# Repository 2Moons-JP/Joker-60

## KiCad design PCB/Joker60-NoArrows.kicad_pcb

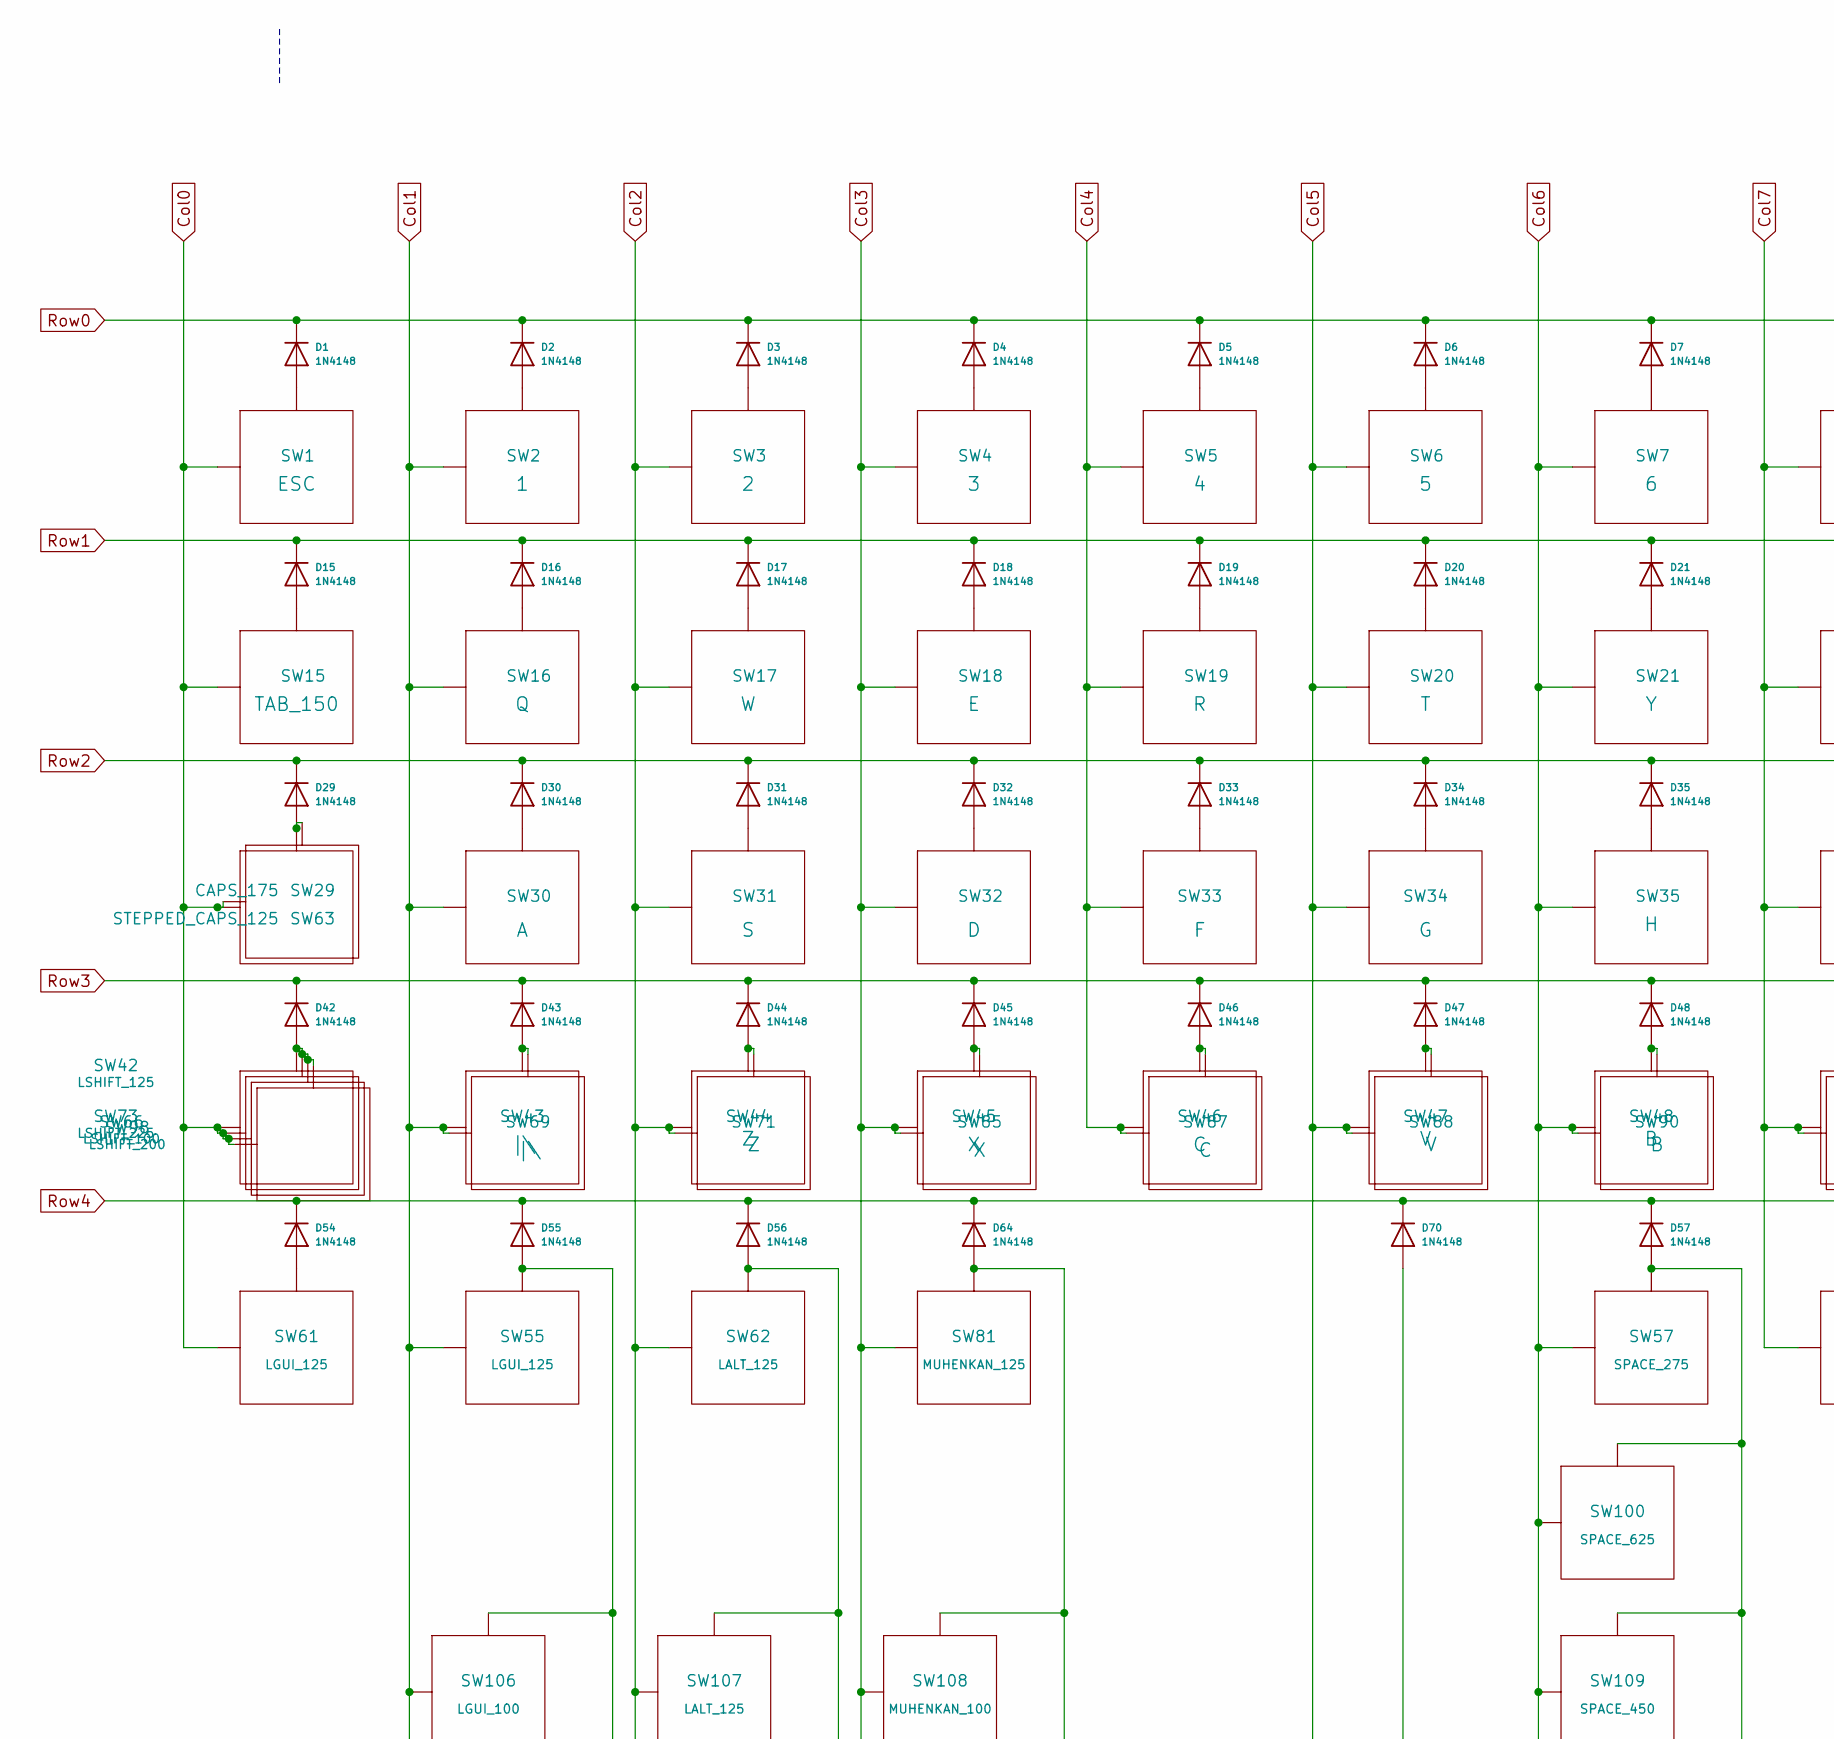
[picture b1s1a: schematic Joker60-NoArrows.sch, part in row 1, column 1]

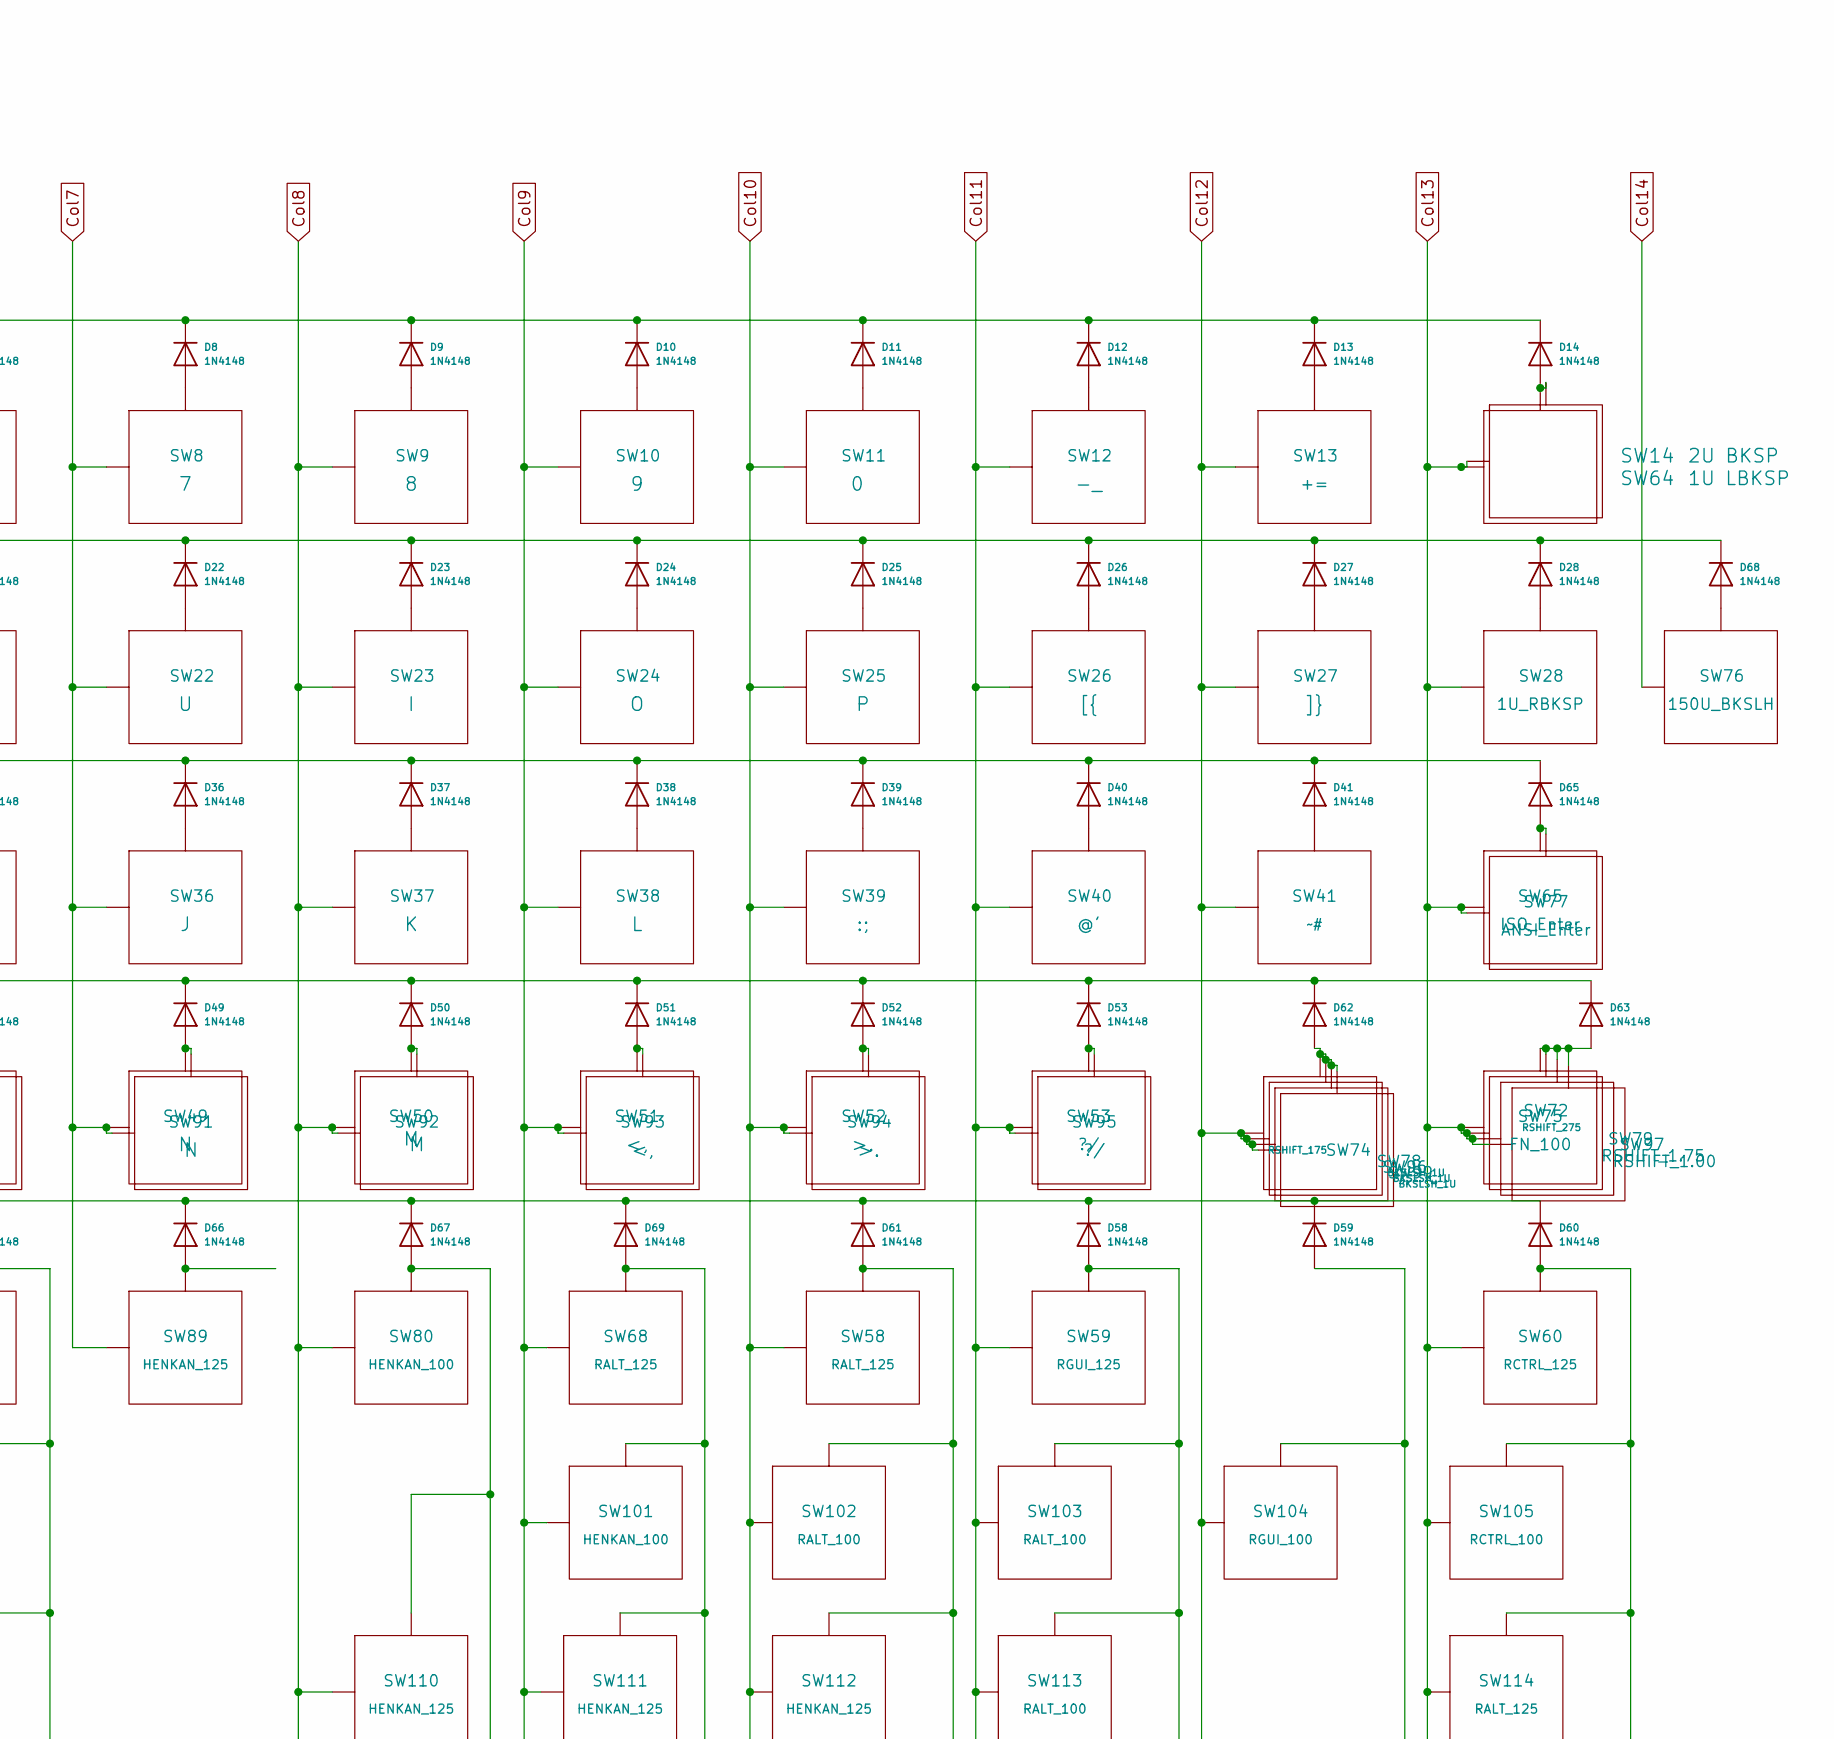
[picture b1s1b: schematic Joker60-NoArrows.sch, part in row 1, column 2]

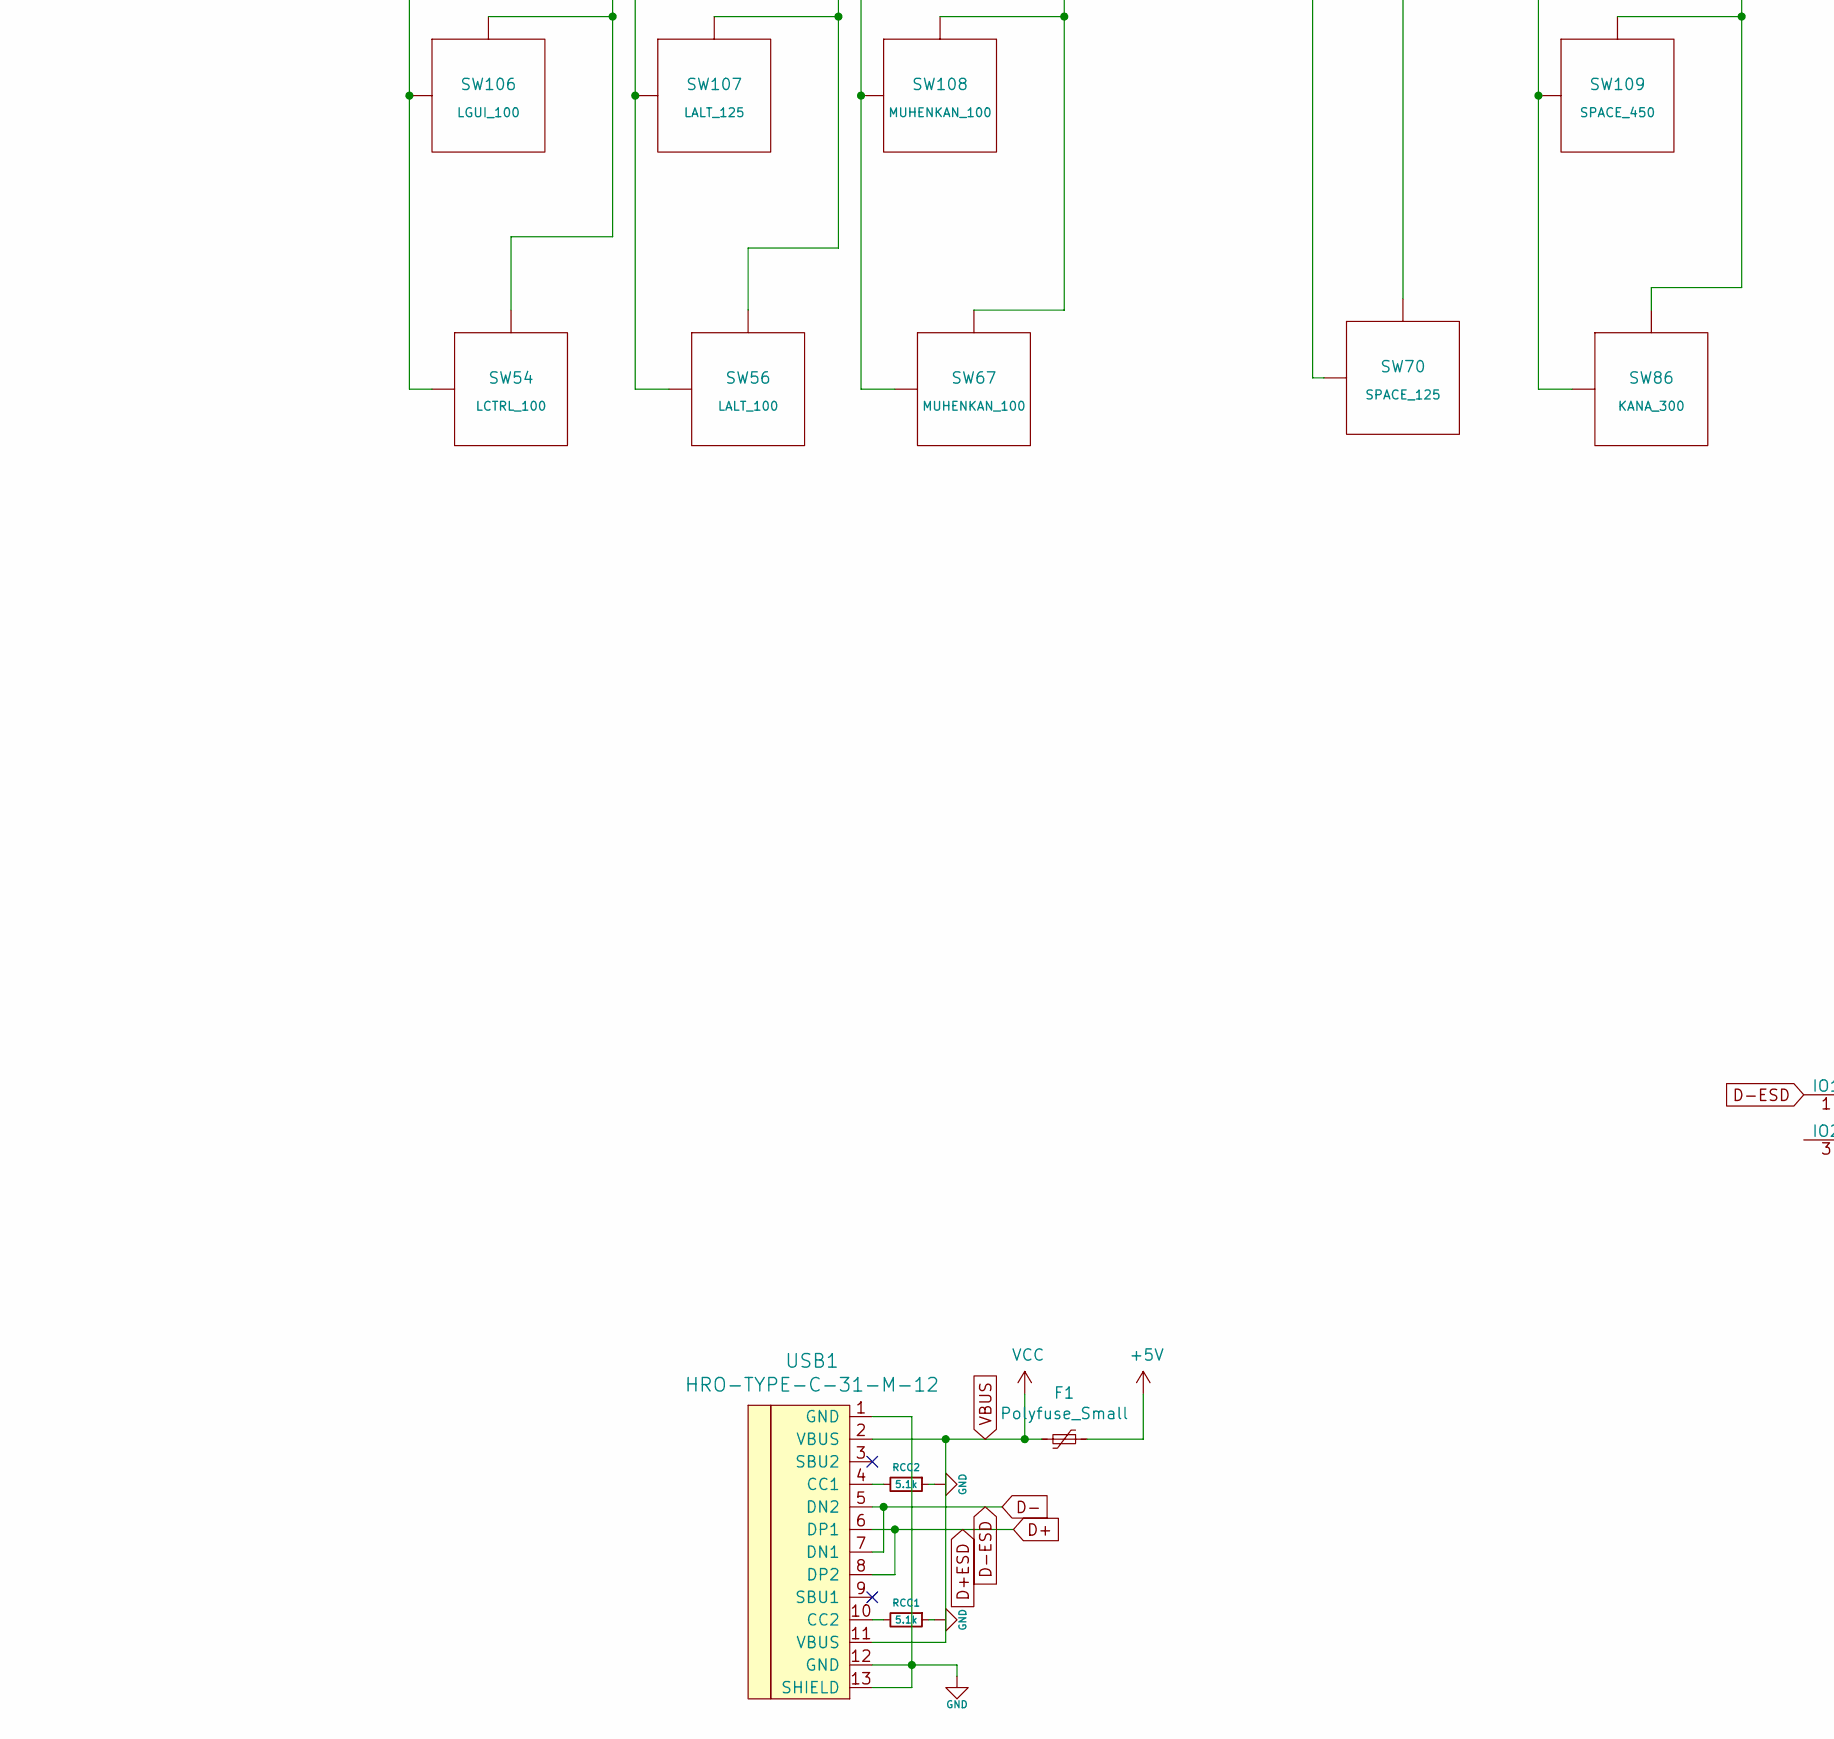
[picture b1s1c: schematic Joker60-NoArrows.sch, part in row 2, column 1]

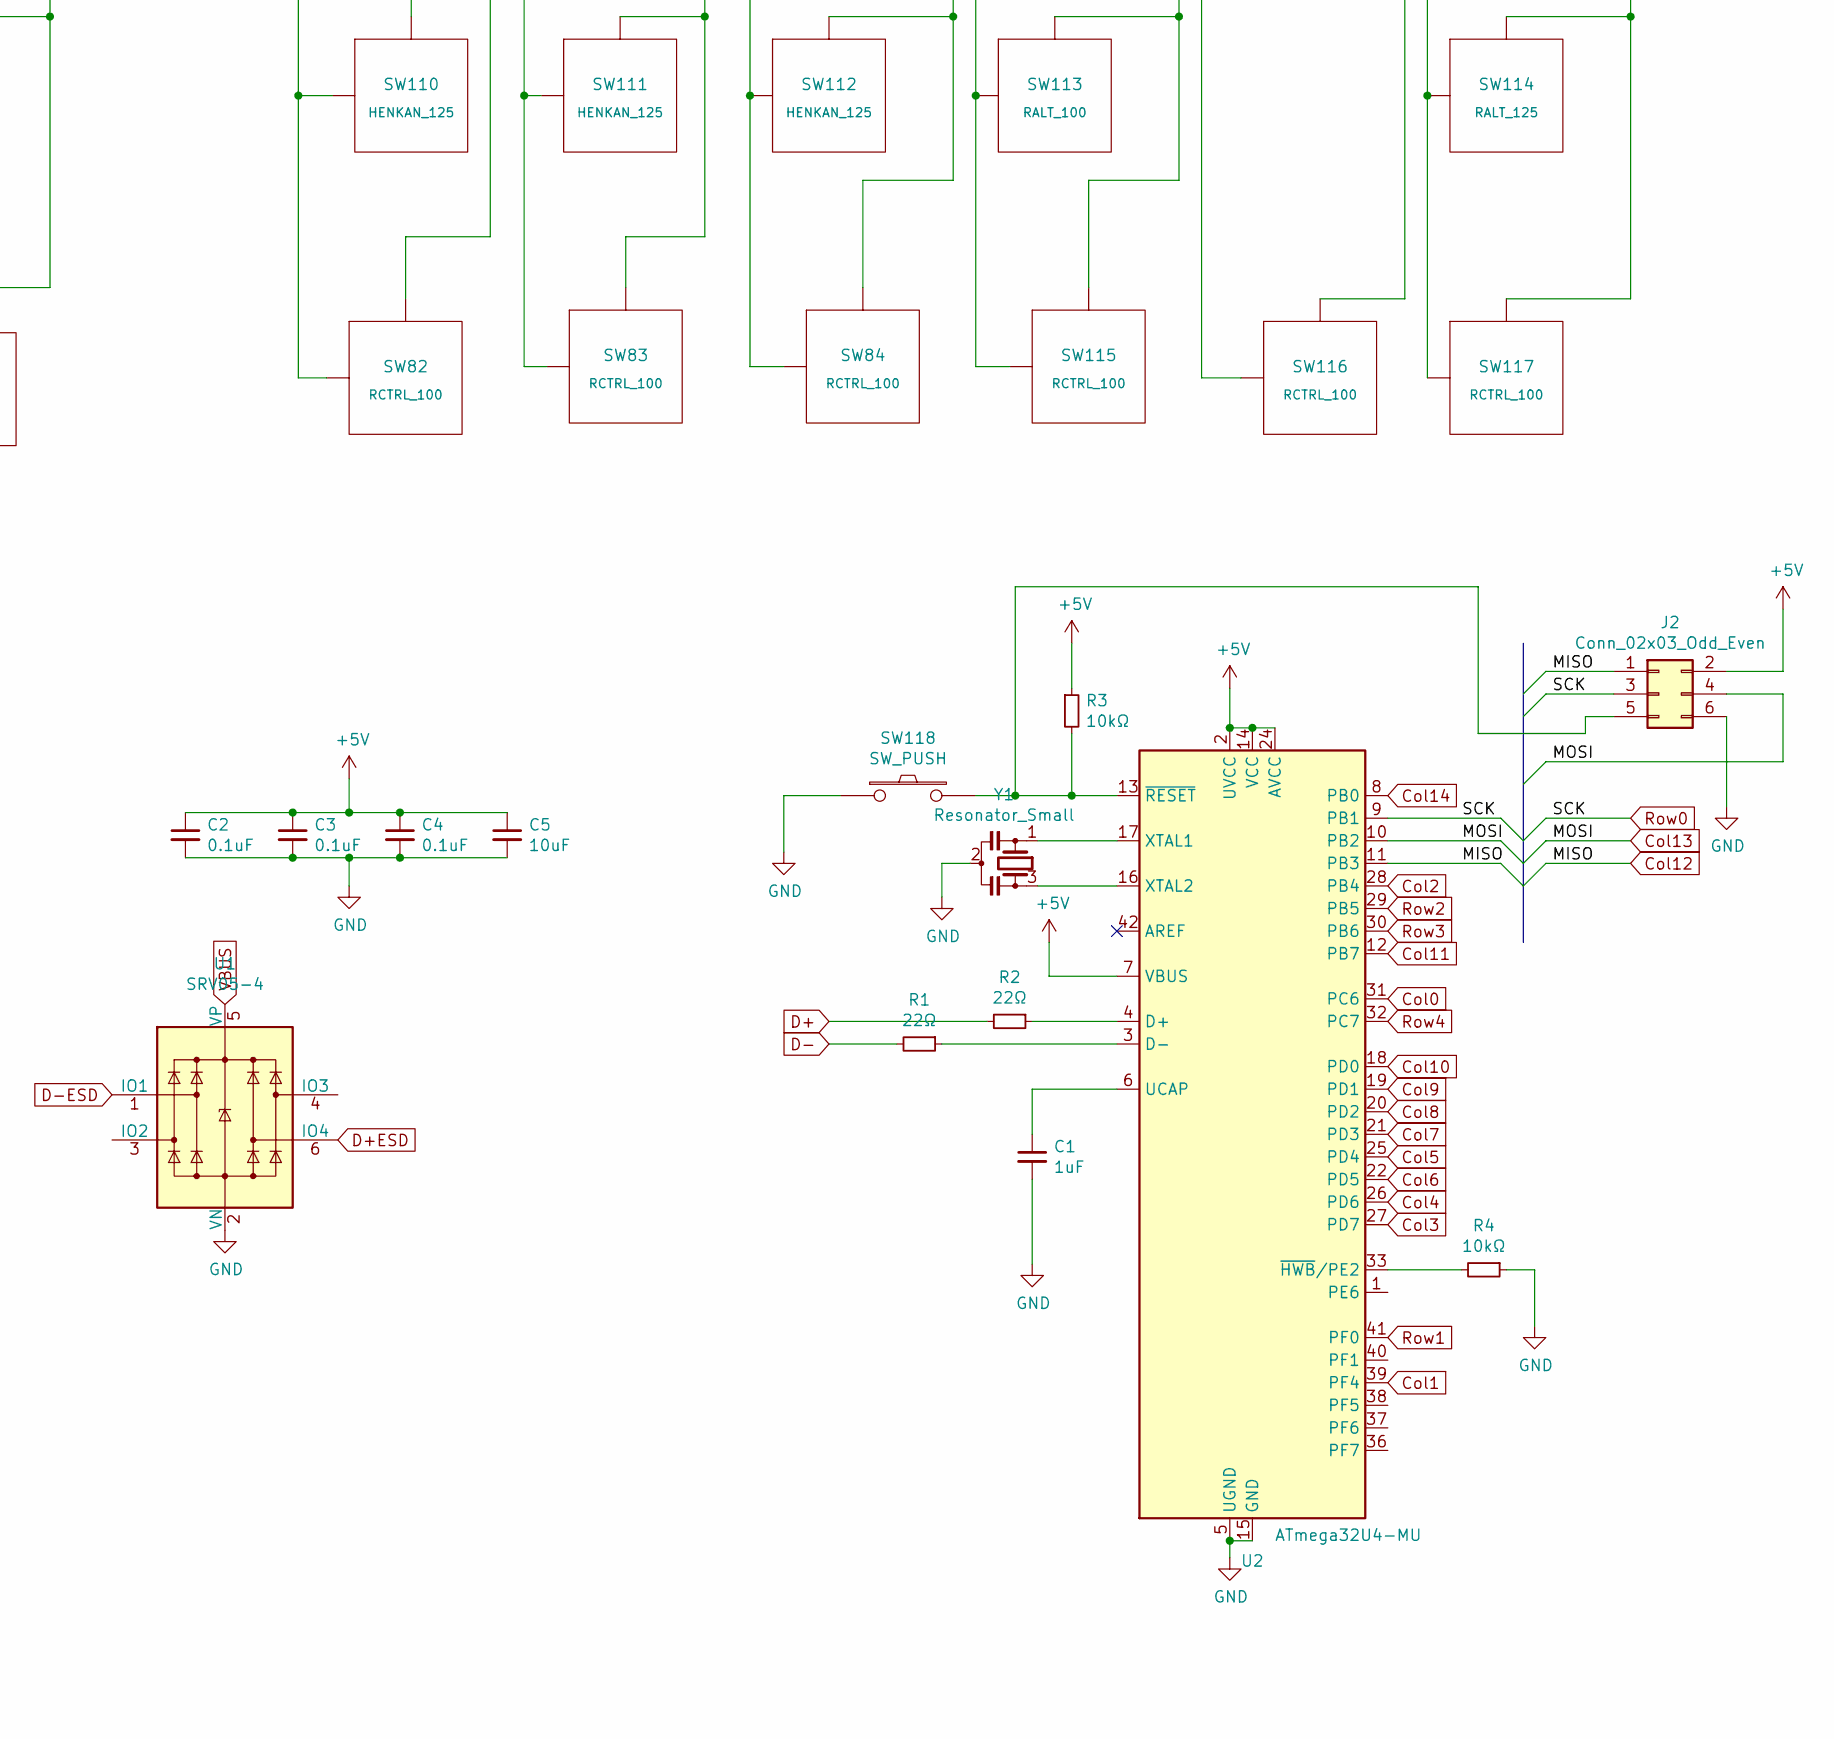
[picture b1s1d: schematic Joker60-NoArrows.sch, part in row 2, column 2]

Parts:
C1: 1uF; C_0603_1608Metric; Part# CL10A105KB8NNNC; LCSC Part# C15849
C2, C3, C4: 0.1uF; C_0603_1608Metric; Part# CC0603KRX7R9BB104; LCSC Part# C14663
C5: 10uF; C_0603_1608Metric; Part# CL10C150JB8NNNC; LCSC Part# C1644
D1, D2, D3, D4, D5, D6, D7, D8, D9, D10, D11, D12, D13, D14, D15, D16, D17, D18, D19, D20, D21, D22, D23, D24, D25, D26, D27, D28, D29, D30, D31, D32, D33, D34, D35, D36, D37, D38, D39, D40, D41, D42, D43, D44, D45, D46, D47, D48, D49, D50, D51, D52, D53, D54, D55, D56, D57, D58, D59, D60, D61, D62, D63, D64, D65, D66, D67, D68, D69, D70: 1N4148; D_SOD-123; Part# 1N4148W; LCSC Part# C444720
F1: Polyfuse_Small; Fuse_0805_2012Metric; Part# nSMD025; LCSC Part# C70068
J2: Conn_02x03_Odd_Even; PinHeader_2x03_P2.54mm_Vertical
R1, R2: 22Ω; R_0603_1608Metric; Part# 0603WAJ0220T5E; LCSC Part# C1203
R3, R4: 10kΩ; R_0603_1608Metric; Part# RMC 0603 10K F N; LCSC Part# C269701
RCC1, RCC2: 5.1k; R_0805_2012Metric; Part# PTFR1206B5K10P9; LCSC Part# C351456
SW1: ESC; MX100
SW2: 1; MX100
SW3: 2; MX100
SW4: 3; MX100
SW5: 4; MX100
SW6: 5; MX100
SW7: 6; MX100
SW8: 7; MX100
SW9: 8; MX100
SW10: 9; MX100
SW11: 0; MX100
SW12: -_; MX100
SW13: +=; MX100
SW14: 2U BKSP; MX200
SW15: TAB_150; MX150
SW16: Q; MX100
SW17: W; MX100
SW18: E; MX100
SW19: R; MX100
SW20: T; MX100
SW21: Y; MX100
SW22: U; MX100
SW23: I; MX100
SW24: O; MX100
SW25: P; MX100
SW26: [{; MX100
SW27: ]}; MX100
SW28: 1U_RBKSP; MX100
SW29: CAPS_175; MX175
SW30: A; MX100
SW31: S; MX100
SW32: D; MX100
SW33: F; MX100
SW34: G; MX100
SW35: H; MX100
SW36: J; MX100
SW37: K; MX100
SW38: L; MX100
SW39: :;; MX100
SW40: @'; MX100
SW41: ~~#; MX100
SW42: LSHIFT_125; MX125
SW43, SW69: |\\; MX100
SW44, SW71: Z; MX100
SW45, SW85: X; MX100
SW46, SW87: C; MX100
SW47, SW88: V; MX100
SW48, SW90: B; MX100
SW49, SW91: N; MX100
SW50, SW92: M; MX100
SW51, SW93: <,; MX100
SW52, SW94: >.; MX100
SW53, SW95: ?/; MX100
SW54: LCTRL_100; MX100
SW55, SW61: LGUI_125; MX125
SW56: LALT_100; MX100
SW57: SPACE_275; MX275R
SW58, SW68, SW114: RALT_125; MX125
SW59: RGUI_125; MX125
SW60: RCTRL_125; MX125
SW62, SW107: LALT_125; MX125
SW63: STEPPED_CAPS_125; MX125
SW64: 1U LBKSP; MX100
SW65: ISO_Enter; MX_ISOEnter_Vertical
SW66: LSHIFT_100; MX100
SW67, SW108: MUHENKAN_100; MX100
SW70: SPACE_125; MX125
SW72: RSHIFT_275; MX275R
SW73: LSHIFT_225; MX225R
SW74: RSHIFT_175; MX175
SW75: FN_100; MX100
SW76: 150U_BKSLH; MX150
SW77: ANSI_Enter; MX225
SW78, SW99: BKSLSH_1U; MX100
SW79: RSHIFT_1.75; MX175
SW80, SW101: HENKAN_100; MX100
SW81: MUHENKAN_125; MX125
SW82, SW83, SW84, SW105, SW115, SW116, SW117: RCTRL_100; MX100
SW86: KANA_300; MX300R
SW89, SW110, SW111, SW112: HENKAN_125; MX125
SW96: BKSLSH_1U; MX200
SW97: RSHIFT_1.00; MX100
SW98: LSHIFT_200; MX200R
SW100: SPACE_625; MX625R
SW102, SW103, SW113: RALT_100; MX100
SW104: RGUI_100; MX100
SW106: LGUI_100; MX100
SW109: SPACE_450; MX450R
SW118: SW_PUSH; SKQG-1155865
U1: SRV05-4; SOT-23-6; Part# SRV05-4; LCSC Part# C558418
U2: ATmega32U4-MU; QFN-44-1EP_7x7mm_P0.5mm_EP5.2x5.2mm; Part# ATMEGA32U4-MU; LCSC Part# C112161
USB1: HRO-TYPE-C-31-M-12; HRO-TYPE-C-31-M-12-Assembly; Part# TYPE-C-31-M-12; LCSC Part# C165948
Y1: Resonator_Small; Resonator_SMD_muRata_CSTxExxV-3Pin_3.0x1.1mm_HandSoldering_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; Part# CSTNE16MOV530000R0; LCSC Part# C341521

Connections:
+5V: C2.1, C3.1, C4.1, C5.1, F1.1, J2.2, R3.1, U2.2 (UVCC), U2.7 (VBUS), U2.14 (VCC), U2.24 (AVCC), U2.34 (VCC), U2.44 (AVCC)
Col0: SW1.1 (Col), SW15.1 (Col), SW29.1 (Col), SW42.1 (Col), SW61.1 (Col), SW63.1 (Col), SW66.1 (Col), SW73.1 (Col), SW98.1 (Col), U2.31 (PC6)
Col1: SW2.1 (Col), SW16.1 (Col), SW30.1 (Col), SW43.1 (Col), SW54.1 (Col), SW55.1 (Col), SW69.1 (Col), SW106.1 (Col), U2.39 (PF4)
Col2: SW3.1 (Col), SW17.1 (Col), SW31.1 (Col), SW44.1 (Col), SW56.1 (Col), SW62.1 (Col), SW71.1 (Col), SW107.1 (Col), U2.28 (PB4)
Col3: SW4.1 (Col), SW18.1 (Col), SW32.1 (Col), SW45.1 (Col), SW67.1 (Col), SW81.1 (Col), SW85.1 (Col), SW108.1 (Col), U2.27 (PD7)
Col4: SW5.1 (Col), SW19.1 (Col), SW33.1 (Col), SW46.1 (Col), SW87.1 (Col), U2.26 (PD6)
Col5: SW6.1 (Col), SW20.1 (Col), SW34.1 (Col), SW47.1 (Col), SW70.1 (Col), SW88.1 (Col), U2.25 (PD4)
Col6: SW7.1 (Col), SW21.1 (Col), SW35.1 (Col), SW48.1 (Col), SW57.1 (Col), SW86.1 (Col), SW90.1 (Col), SW100.1 (Col), SW109.1 (Col), U2.22 (PD5)
Col7: SW8.1 (Col), SW22.1 (Col), SW36.1 (Col), SW49.1 (Col), SW89.1 (Col), SW91.1 (Col), U2.21 (PD3)
Col8: SW9.1 (Col), SW23.1 (Col), SW37.1 (Col), SW50.1 (Col), SW80.1 (Col), SW82.1 (Col), SW92.1 (Col), SW110.1 (Col), U2.20 (PD2)
Col9: SW10.1 (Col), SW24.1 (Col), SW38.1 (Col), SW51.1 (Col), SW68.1 (Col), SW83.1 (Col), SW93.1 (Col), SW101.1 (Col), SW111.1 (Col), U2.19 (PD1)
Col10: SW11.1 (Col), SW25.1 (Col), SW39.1 (Col), SW52.1 (Col), SW58.1 (Col), SW84.1 (Col), SW94.1 (Col), SW102.1 (Col), SW112.1 (Col), U2.18 (PD0)
Col11: SW12.1 (Col), SW26.1 (Col), SW40.1 (Col), SW53.1 (Col), SW59.1 (Col), SW95.1 (Col), SW103.1 (Col), SW113.1 (Col), SW115.1 (Col), U2.12 (PB7)
Col12: J2.1, SW13.1 (Col), SW27.1 (Col), SW41.1 (Col), SW74.1 (Col), SW78.1 (Col), SW96.1 (Col), SW99.1 (Col), SW104.1 (Col), SW116.1 (Col), U2.11 (PB3)
Col13: J2.4, SW14.1 (Col), SW28.1 (Col), SW60.1 (Col), SW64.1 (Col), SW65.1 (Col), SW72.1 (Col), SW75.1 (Col), SW77.1 (Col), SW79.1 (Col), SW97.1 (Col), SW105.1 (Col), SW114.1 (Col), SW117.1 (Col), U2.10 (PB2)
Col14: SW76.1 (Col), U2.8 (PB0)
D+: R2.2, U1.6 (IO4), USB1.6 (DP1), USB1.8 (DP2)
D-: R1.2, U1.1 (IO1), USB1.5 (DN2), USB1.7 (DN1)
GND: C1.2, C2.2, C3.2, C4.2, C5.2, J2.6, R4.1, RCC1.1, RCC2.1, SW118.1, U1.2 (VN), U2.5 (UGND), U2.15 (GND), U2.23 (GND), U2.35 (GND), U2.43 (GND), U2.45 (GND), USB1.1 (GND), USB1.12 (GND), USB1.13 (SHIELD), Y1.2
unnamed: C1.1, U2.6 (UCAP)
unnamed: D1.2 (A), SW1.2 (Row)
unnamed: D2.2 (A), SW2.2 (Row)
unnamed: D3.2 (A), SW3.2 (Row)
unnamed: D4.2 (A), SW4.2 (Row)
unnamed: D5.2 (A), SW5.2 (Row)
unnamed: D6.2 (A), SW6.2 (Row)
unnamed: D7.2 (A), SW7.2 (Row)
unnamed: D8.2 (A), SW8.2 (Row)
unnamed: D9.2 (A), SW9.2 (Row)
unnamed: D10.2 (A), SW10.2 (Row)
unnamed: D11.2 (A), SW11.2 (Row)
unnamed: D12.2 (A), SW12.2 (Row)
unnamed: D13.2 (A), SW13.2 (Row)
unnamed: D14.2 (A), SW14.2 (Row), SW64.2 (Row)
unnamed: D15.2 (A), SW15.2 (Row)
unnamed: D16.2 (A), SW16.2 (Row)
unnamed: D17.2 (A), SW17.2 (Row)
unnamed: D18.2 (A), SW18.2 (Row)
unnamed: D19.2 (A), SW19.2 (Row)
unnamed: D20.2 (A), SW20.2 (Row)
unnamed: D21.2 (A), SW21.2 (Row)
unnamed: D22.2 (A), SW22.2 (Row)
unnamed: D23.2 (A), SW23.2 (Row)
unnamed: D24.2 (A), SW24.2 (Row)
unnamed: D25.2 (A), SW25.2 (Row)
unnamed: D26.2 (A), SW26.2 (Row)
unnamed: D27.2 (A), SW27.2 (Row)
unnamed: D28.2 (A), SW28.2 (Row)
unnamed: D29.2 (A), SW29.2 (Row), SW63.2 (Row)
unnamed: D30.2 (A), SW30.2 (Row)
unnamed: D31.2 (A), SW31.2 (Row)
unnamed: D32.2 (A), SW32.2 (Row)
unnamed: D33.2 (A), SW33.2 (Row)
unnamed: D34.2 (A), SW34.2 (Row)
unnamed: D35.2 (A), SW35.2 (Row)
unnamed: D36.2 (A), SW36.2 (Row)
unnamed: D37.2 (A), SW37.2 (Row)
unnamed: D38.2 (A), SW38.2 (Row)
unnamed: D39.2 (A), SW39.2 (Row)
unnamed: D40.2 (A), SW40.2 (Row)
unnamed: D41.2 (A), SW41.2 (Row)
unnamed: D42.2 (A), SW42.2 (Row), SW66.2 (Row), SW73.2 (Row), SW98.2 (Row)
unnamed: D43.2 (A), SW43.2 (Row), SW69.2 (Row)
unnamed: D44.2 (A), SW44.2 (Row), SW71.2 (Row)
unnamed: D45.2 (A), SW45.2 (Row), SW85.2 (Row)
unnamed: D46.2 (A), SW46.2 (Row), SW87.2 (Row)
unnamed: D47.2 (A), SW47.2 (Row), SW88.2 (Row)
unnamed: D48.2 (A), SW48.2 (Row), SW90.2 (Row)
unnamed: D49.2 (A), SW49.2 (Row), SW91.2 (Row)
unnamed: D50.2 (A), SW50.2 (Row), SW92.2 (Row)
unnamed: D51.2 (A), SW51.2 (Row), SW93.2 (Row)
unnamed: D52.2 (A), SW52.2 (Row), SW94.2 (Row)
unnamed: D53.2 (A), SW53.2 (Row), SW95.2 (Row)
unnamed: D54.2 (A), SW61.2 (Row)
unnamed: D55.2 (A), SW54.2 (Row), SW55.2 (Row), SW106.2 (Row)
unnamed: D56.2 (A), SW56.2 (Row), SW62.2 (Row), SW107.2 (Row)
unnamed: D57.2 (A), SW57.2 (Row), SW86.2 (Row), SW100.2 (Row), SW109.2 (Row)
unnamed: D58.2 (A), SW59.2 (Row), SW103.2 (Row), SW113.2 (Row), SW115.2 (Row)
unnamed: D59.2 (A), SW104.2 (Row), SW116.2 (Row)
unnamed: D60.2 (A), SW60.2 (Row), SW105.2 (Row), SW114.2 (Row), SW117.2 (Row)
unnamed: D61.2 (A), SW58.2 (Row), SW84.2 (Row), SW102.2 (Row), SW112.2 (Row)
unnamed: D62.2 (A), SW74.2 (Row), SW78.2 (Row), SW96.2 (Row), SW99.2 (Row)
unnamed: D63.2 (A), SW72.2 (Row), SW75.2 (Row), SW79.2 (Row), SW97.2 (Row)
unnamed: D64.2 (A), SW67.2 (Row), SW81.2 (Row), SW108.2 (Row)
unnamed: D65.2 (A), SW65.2 (Row), SW77.2 (Row)
unnamed: D66.2 (A), SW89.2 (Row)
unnamed: D67.2 (A), SW80.2 (Row), SW82.2 (Row), SW110.2 (Row)
unnamed: D68.2 (A), SW76.2 (Row)
unnamed: D69.2 (A), SW68.2 (Row), SW83.2 (Row), SW101.2 (Row), SW111.2 (Row)
unnamed: D70.2 (A), SW70.2 (Row)
unnamed: J2.5, R3.2, SW118.2, U2.13 (~RESET)
unnamed: R1.1, U2.3 (D-)
unnamed: R2.1, U2.4 (D+)
unnamed: R4.2, U2.33 (~HWB~/PE2)
unnamed: RCC1.2, USB1.10 (CC2)
unnamed: RCC2.2, USB1.4 (CC1)
unnamed: U2.16 (XTAL2), Y1.3
unnamed: U2.17 (XTAL1), Y1.1
Row0: D1.1 (K), D2.1 (K), D3.1 (K), D4.1 (K), D5.1 (K), D6.1 (K), D7.1 (K), D8.1 (K), D9.1 (K), D10.1 (K), D11.1 (K), D12.1 (K), D13.1 (K), D14.1 (K), J2.3, U2.9 (PB1)
Row1: D15.1 (K), D16.1 (K), D17.1 (K), D18.1 (K), D19.1 (K), D20.1 (K), D21.1 (K), D22.1 (K), D23.1 (K), D24.1 (K), D25.1 (K), D26.1 (K), D27.1 (K), D28.1 (K), D68.1 (K), U2.41 (PF0)
Row2: D29.1 (K), D30.1 (K), D31.1 (K), D32.1 (K), D33.1 (K), D34.1 (K), D35.1 (K), D36.1 (K), D37.1 (K), D38.1 (K), D39.1 (K), D40.1 (K), D41.1 (K), D65.1 (K), U2.29 (PB5)
Row3: D42.1 (K), D43.1 (K), D44.1 (K), D45.1 (K), D46.1 (K), D47.1 (K), D48.1 (K), D49.1 (K), D50.1 (K), D51.1 (K), D52.1 (K), D53.1 (K), D62.1 (K), D63.1 (K), U2.30 (PB6)
Row4: D54.1 (K), D55.1 (K), D56.1 (K), D57.1 (K), D58.1 (K), D59.1 (K), D60.1 (K), D61.1 (K), D64.1 (K), D66.1 (K), D67.1 (K), D69.1 (K), D70.1 (K), U2.32 (PC7)
VBUS: F1.2, U1.5 (VP), USB1.2 (VBUS), USB1.11 (VBUS)

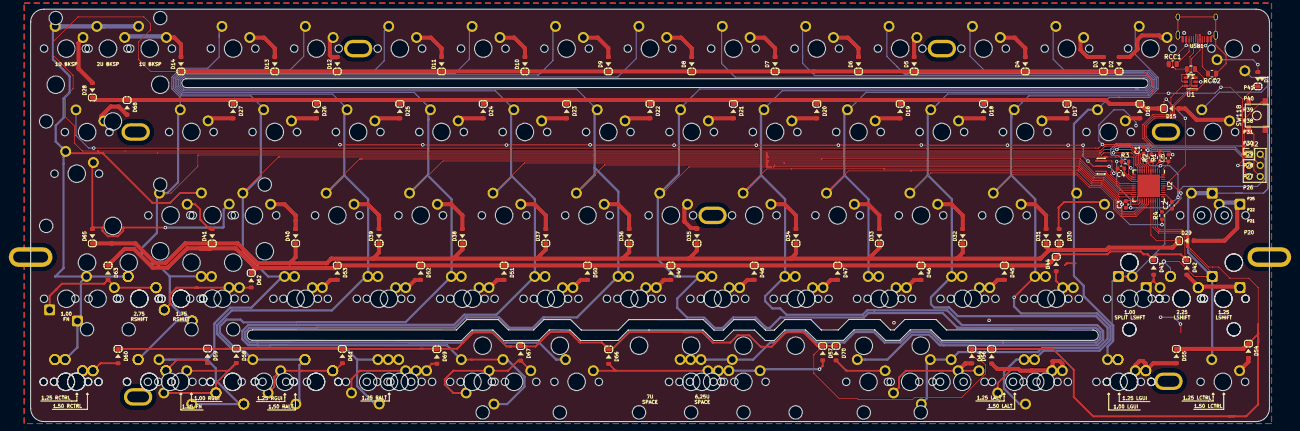
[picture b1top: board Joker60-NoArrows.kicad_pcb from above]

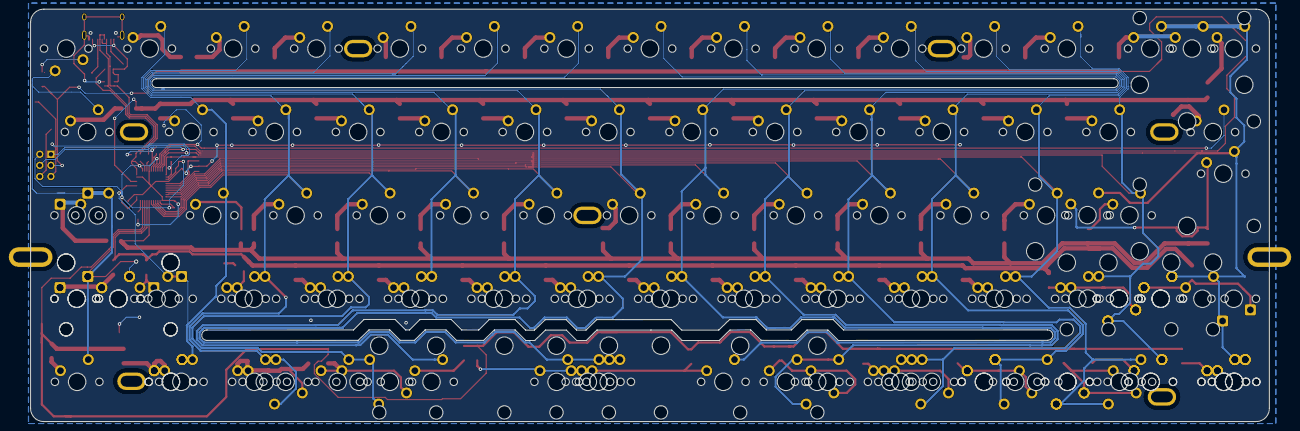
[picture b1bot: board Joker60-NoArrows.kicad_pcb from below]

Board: 2 copper layers, 283.0 x 94.2 mm, 214 parts (5 on the bottom side), 104 nets.

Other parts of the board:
H1, H6: Half Side Hole; halfSideHole
H2: Mounting Hole; MoutingHole_Oval_7mm_5.0x2.5mm
H3, H5, H7, H8, H9, H10: Oval Mounting Hole; MoutingHole_Oval_7mm_5.0x2.5mm

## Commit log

2021-01-24 PCB Complete
2021-02-07 2/8/2021
2021-02-09 Manu Prep
2021-02-12 2/12/221
2021-03-12 Gerber
2021-08-29 8/29
2021-10-06 10/7
2021-12-20 12/20
